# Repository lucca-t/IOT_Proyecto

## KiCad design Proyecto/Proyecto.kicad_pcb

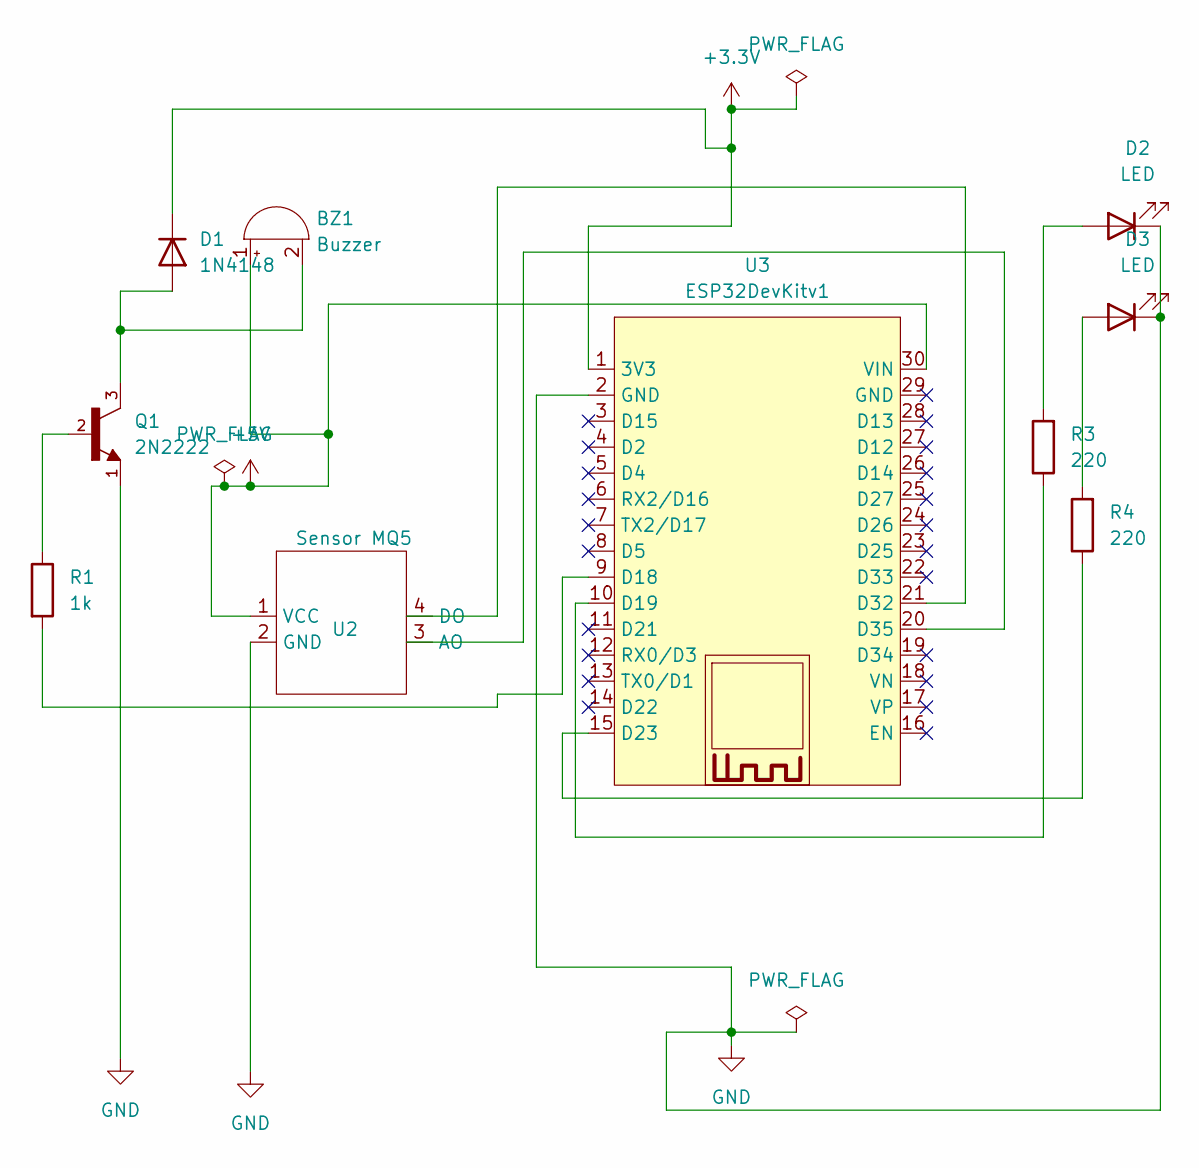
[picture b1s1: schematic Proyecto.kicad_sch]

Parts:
BZ1: Buzzer; Buzzer_12x9.5RM7.6
D1: 1N4148; D_DO-35_SOD27_P7.62mm_Horizontal
D2, D3: LED; LED_D3.0mm
Q1: 2N2222; TO127P584H533-3; PARTREV R2
R1: 1k; R_Axial_DIN0207_L6.3mm_D2.5mm_P7.62mm_Horizontal
R3, R4: 220; R_Axial_DIN0207_L6.3mm_D2.5mm_P7.62mm_Horizontal
U2: Sensor MQ5; MQ5
U3: ESP32DevKitv1

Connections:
+3.3V: D1.1 (K), U3.1 (3V3)
+5V: BZ1.1 (+), U2.1 (VCC), U3.30 (VIN)
GND: D2.1 (K), D3.1 (K), Q1.1, U2.2 (GND), U3.2 (GND)
unnamed: BZ1.2 (-), D1.2 (A), Q1.3
unnamed: D2.2 (A), R3.2
unnamed: D3.2 (A), R4.2
unnamed: Q1.2, R1.1
unnamed: U2.3 (AO), U3.20 (D35)
unnamed: U2.4 (DO), U3.21 (D32)
unnamed: R1.2, U3.9 (D18)
unnamed: R3.1, U3.10 (D19)
unnamed: R4.1, U3.15 (D23)

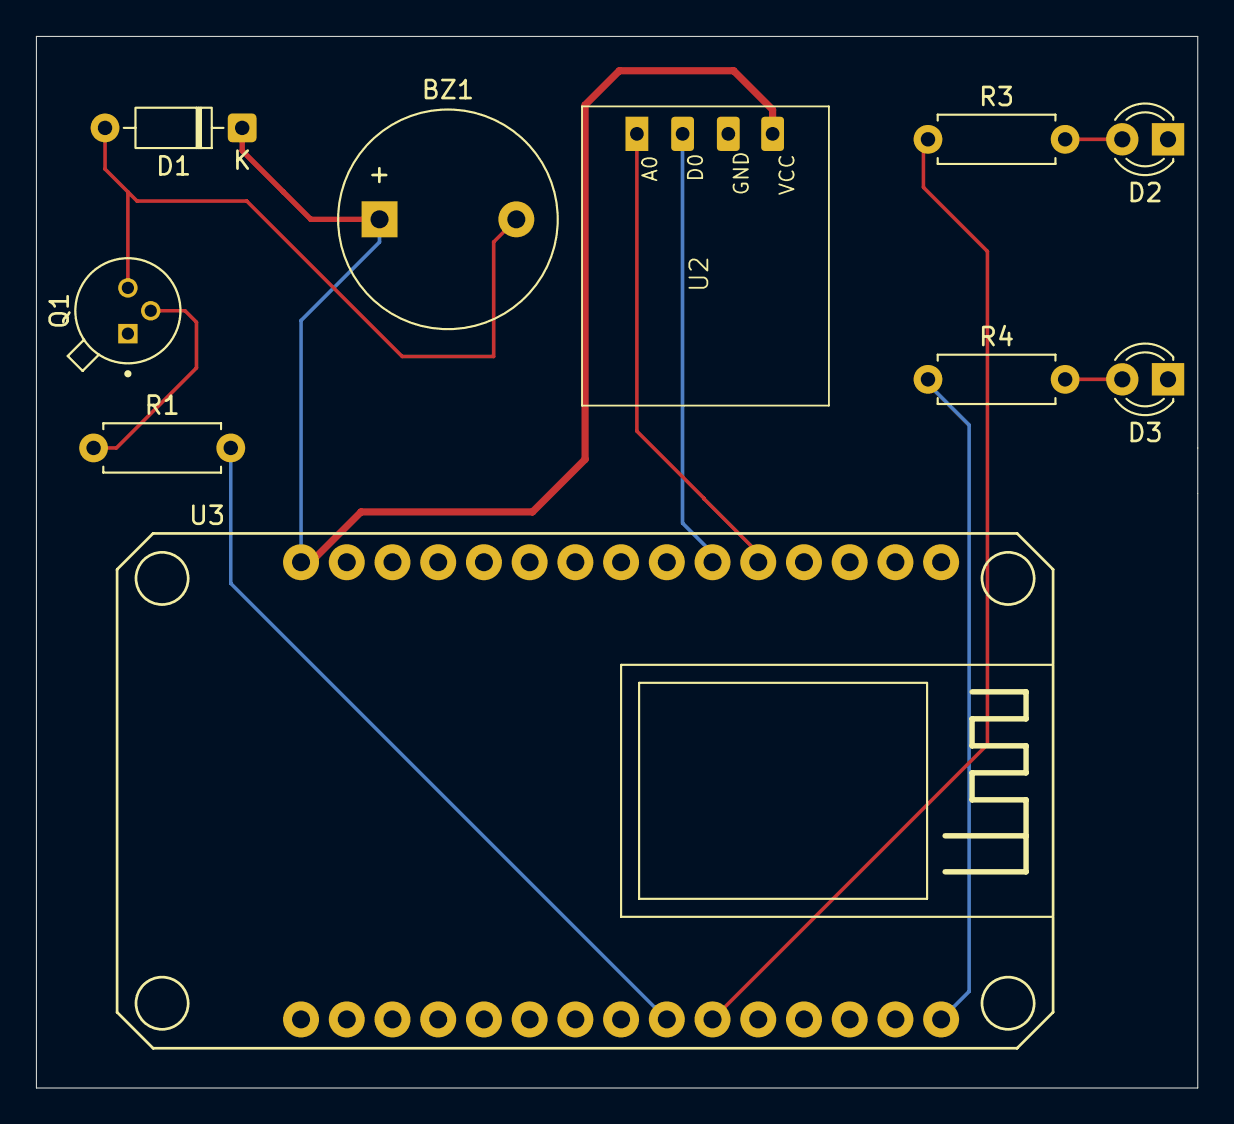
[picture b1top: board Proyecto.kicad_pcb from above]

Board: 2 copper layers, 64.5 x 58.4 mm, 10 parts (0 on the bottom side), 12 nets.

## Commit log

2025-11-25 Primer intento
2025-11-27 listo
2025-11-29 version final final v2.0.1 FINAL en serio 1 (1) (2)
